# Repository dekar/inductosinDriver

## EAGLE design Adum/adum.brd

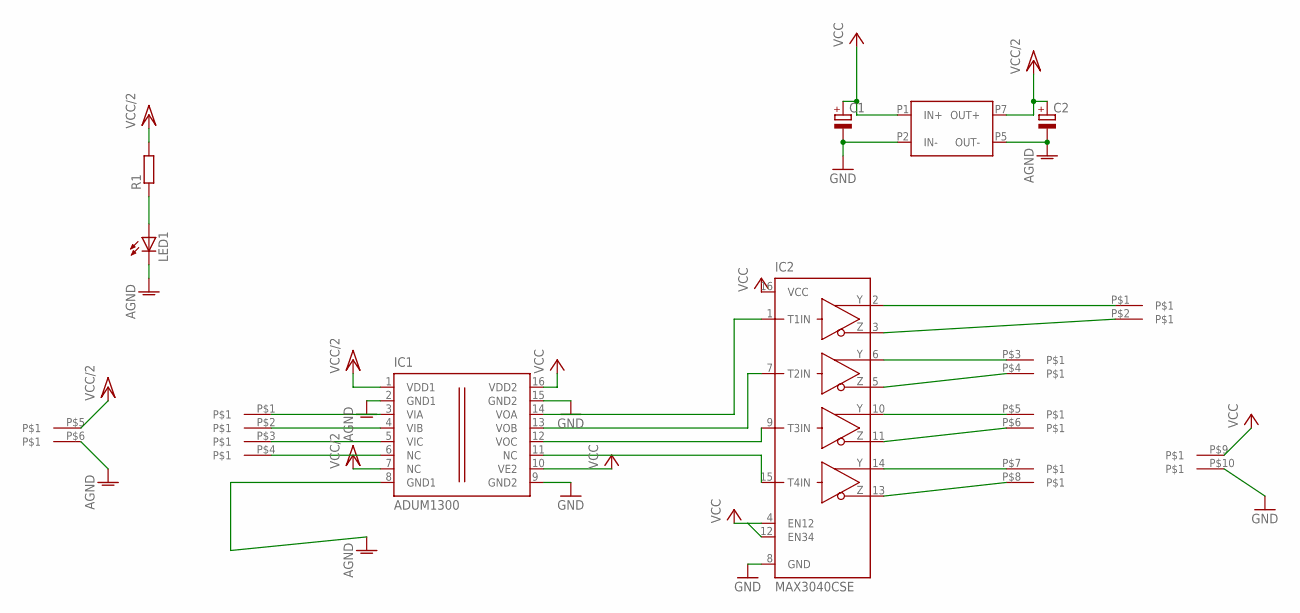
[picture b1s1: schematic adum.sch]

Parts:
C1, C2: CPOL-EUSMCD; SMC_D
IC1: ADUM1300; SO-16W
IC2: MAX3040CSE; SO16
LED1: LEDCHIP-LED0805; CHIP-LED0805
R1: R-EU_M0805; M0805
U$1: 2X5
U$2: 2X3
U$3: DCDC; PWR

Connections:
AGND: C2.-, IC1.2 (GND1), IC1.8 (GND1), LED1.C, U$2.P$6, U$3.P5 (OUT-)
GND: C1.-, IC1.9 (GND2), IC1.15 (GND2), IC2.8 (GND), U$1.P$10, U$3.P2 (IN-)
unnamed: IC1.14 (VOA), IC2.1 (T1IN)
unnamed: IC1.13 (VOB), IC2.7 (T2IN)
unnamed: IC1.12 (VOC), IC2.9 (T3IN)
unnamed: IC1.11 (NC), IC2.15 (T4IN)
unnamed: IC2.3 (Z1), U$1.P$2
unnamed: IC2.2 (Y1), U$1.P$1
unnamed: IC2.11 (Z3), U$1.P$6
unnamed: IC1.6 (NC), U$2.P$4
unnamed: IC1.5 (VIC), U$2.P$3
unnamed: IC2.10 (Y3), U$1.P$5
unnamed: IC1.4 (VIB), U$2.P$2
unnamed: IC2.14 (Y4), U$1.P$7
unnamed: IC2.6 (Y2), U$1.P$3
unnamed: IC1.3 (VIA), U$2.P$1
unnamed: IC2.5 (Z2), U$1.P$4
unnamed: LED1.A, R1.1
unnamed: IC2.13 (Z4), U$1.P$8
VCC: C1.+, IC1.10 (VE2), IC1.16 (VDD2), IC2.4 (EN12), IC2.12 (EN34), IC2.16 (VCC), U$1.P$9, U$3.P1 (IN+)
VCC/2: C2.+, IC1.1 (VDD1), IC1.7 (NC), R1.2, U$2.P$5, U$3.P7 (OUT+)

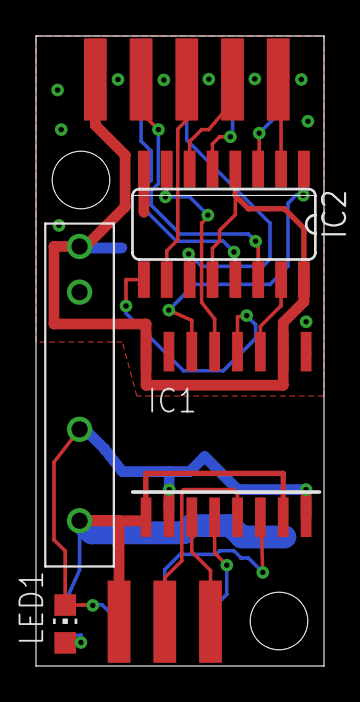
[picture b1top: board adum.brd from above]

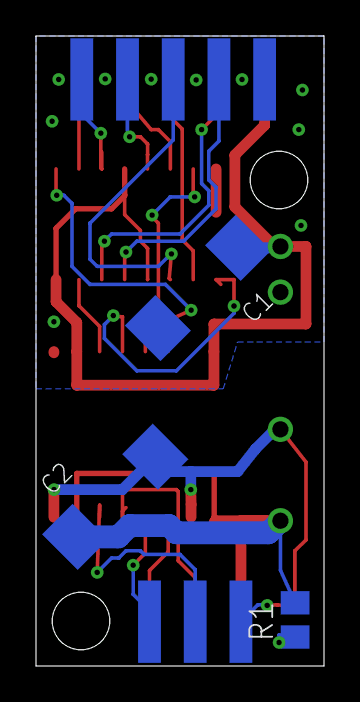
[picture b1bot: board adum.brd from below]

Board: 2 copper layers, 16.0 x 35.0 mm, 9 parts (3 on the bottom side), 21 nets.

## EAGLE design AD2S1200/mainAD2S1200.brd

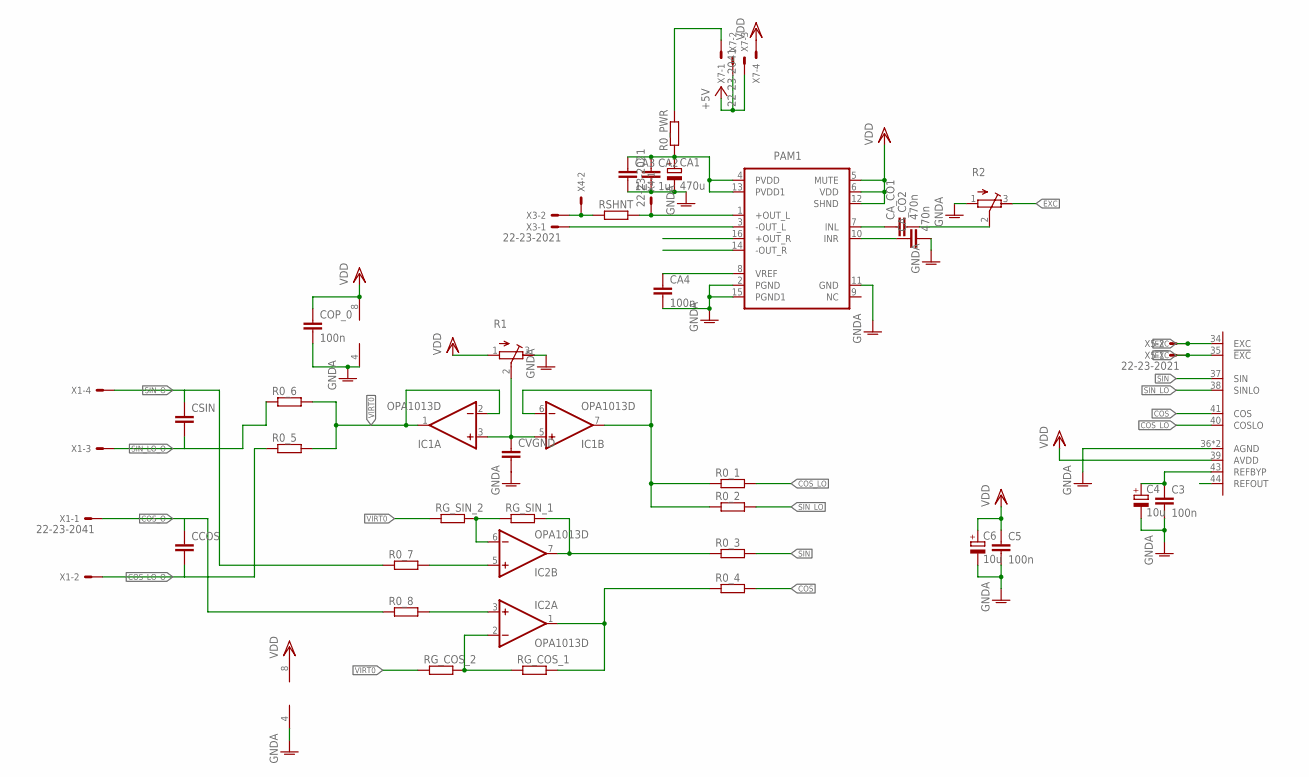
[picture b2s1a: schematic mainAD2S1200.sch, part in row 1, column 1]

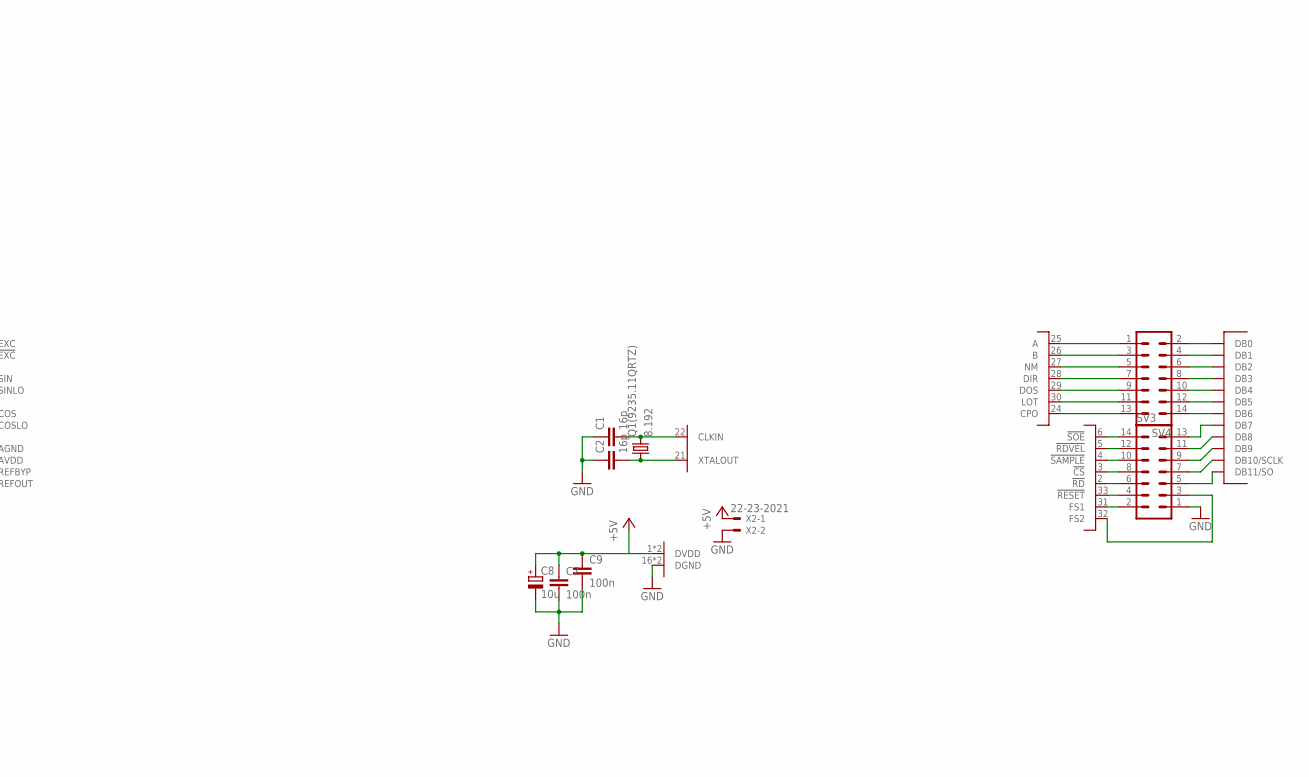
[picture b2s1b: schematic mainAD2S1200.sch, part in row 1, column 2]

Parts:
C1, C2: 16p; C0805
C3, C5, C7, C9: 100n; C0805
C4, C6, C8: 10u; SMC_A
CA1: 470u; EB25D
CA2, CA3: 1u; C1206
CA4: 100n; C0805
CA_CO1, CA_CO2: 470n; C0805
CCOS: C-EUC0805; C0805
COP_0: 100n; C0805
CSIN: C-EUC0805; C0805
CVGND: C-EUC0805; C0805
IC1, IC2: OPA1013D; SO08
PAM1: PAM8403; SOP-16
Q1(9235.11QRTZ): 8.192; CTS406
R0_1, R0_2, R0_3, R0_4, R0_5, R0_6, R0_7, R0_8, R0_PWR: R-EU_R0805; R0805
R1, R2: R-TRIMM64X; RTRIM64X
RG_COS_1, RG_COS_2: R-EU_R0805; R0805
RG_SIN_1, RG_SIN_2: R-EU_R0805; R0805
RSHNT: R-EU_R0805; R0805
SV3, SV4: ML14
U$1: AD1S1200; TQFP-44
X1, X7: 22-23-2041
X2, X3, X4, X5: 22-23-2021

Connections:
!EXC: U$1.35 (!EXC), X5.1
+5V: C7.1, C8.+, C9.1, U$1.1 (DVDD), U$1.17 (DVDD), X2.1, X7.2, X7.3
COS: R0_4.2, U$1.41 (COS)
COS_LO: R0_1.2, U$1.40 (COSLO)
COS_LO_O: CCOS.2, R0_5.1, X1.2
COS_O: CCOS.1, R0_8.1, X1.1
EXC: R2.3 (E), U$1.34 (EXC), X5.2
GND: C1.1, C2.1, C7.2, C8.-, C9.2, SV3.1, U$1.16 (DGND), U$1.23 (DGND), X2.2
GNDA: C3.2, C4.-, C5.2, C6.-, CA1.-, CA2.2, CA3.2, CA4.2, CA_CO2.2, COP_0.2, CVGND.2, IC1.4 (V-), IC2.4 (V-), PAM1.2 (PGND), PAM1.11 (GND), PAM1.15 (PGND1), R1.3 (E), R2.1 (A), U$1.36 (AGND), U$1.42 (AGND)
unnamed: C1.2, Q1(9235.11QRTZ).3 (2), U$1.22 (CLKIN)
unnamed: C2.2, Q1(9235.11QRTZ).1, U$1.21 (XTALOUT)
unnamed: CA4.1, PAM1.8 (VREF)
unnamed: CA_CO1.1, PAM1.7 (INL)
unnamed: C3.1, C4.+, U$1.43 (REFBYP)
unnamed: CA_CO2.1, PAM1.10 (INR)
unnamed: IC1.6 (-IN), IC1.7 (OUT), R0_1.1, R0_2.1
unnamed: PAM1.1 (+OUT_L), RSHNT.2, X4.1
unnamed: PAM1.3 (-OUT_L), X3.1
unnamed: IC2.7 (OUT), R0_3.1, RG_SIN_1.2
unnamed: IC2.1 (OUT), R0_4.1, RG_COS_1.2
unnamed: CVGND.1, IC1.3 (+IN), IC1.5 (+IN), R1.2 (S)
unnamed: SV4.2, U$1.20 (DB0)
unnamed: IC2.5 (+IN), R0_7.2
unnamed: IC2.3 (+IN), R0_8.2
unnamed: SV4.4, U$1.19 (DB1)
unnamed: IC2.6 (-IN), RG_SIN_1.1, RG_SIN_2.2
unnamed: IC2.2 (-IN), RG_COS_1.1, RG_COS_2.2
unnamed: SV4.6, U$1.18 (DB2)
unnamed: SV4.12, U$1.13 (DB5)
unnamed: SV4.14, U$1.12 (DB6)
unnamed: SV4.8, U$1.15 (DB3)
unnamed: SV4.10, U$1.14 (DB4)
unnamed: SV3.5, U$1.7 (DB11/SO)
unnamed: SV3.7, U$1.8 (DB10/SCLK)
unnamed: SV3.9, U$1.9 (DB9)
unnamed: SV3.11, U$1.10 (DB8)
unnamed: SV3.13, U$1.11 (DB7)
unnamed: SV4.11, U$1.30 (LOT)
unnamed: SV4.7, U$1.28 (DIR)
unnamed: SV4.9, U$1.29 (DOS)
unnamed: SV4.5, U$1.27 (NM)
unnamed: SV4.3, U$1.26 (B)
unnamed: SV4.1, U$1.25 (A)
unnamed: SV4.13, U$1.24 (CPO)
unnamed: SV3.6, U$1.2 (!RD)
unnamed: SV3.8, U$1.3 (!CS)
unnamed: SV3.10, U$1.4 (!SAMPLE)
unnamed: SV3.12, U$1.5 (!RDVEL)
unnamed: SV3.14, U$1.6 (!SOE)
unnamed: SV3.4, U$1.33 (!RESET)
unnamed: SV3.2, U$1.31 (FS1)
unnamed: SV3.3, U$1.32 (FS2)
unnamed: CA_CO1.2, R2.2 (S)
unnamed: RSHNT.1, X3.2, X4.2
unnamed: CA1.+, CA2.1, CA3.1, PAM1.4 (PVDD), PAM1.13 (PVDD1), R0_PWR.1
unnamed: R0_PWR.2, X7.1
SIN: R0_3.2, U$1.37 (SIN)
SIN_LO: R0_2.2, U$1.38 (SINLO)
SIN_LO_O: CSIN.2, R0_6.1, X1.3
SIN_O: CSIN.1, R0_7.1, X1.4
VDD: C5.1, C6.+, COP_0.1, IC1.8 (V+), IC2.8 (V+), PAM1.5 (MUTE), PAM1.6 (VDD), PAM1.12 (SHND), R1.1 (A), U$1.39 (AVDD), X7.4
VIRT0: IC1.1 (OUT), IC1.2 (-IN), R0_5.2, R0_6.2, RG_COS_2.1, RG_SIN_2.1

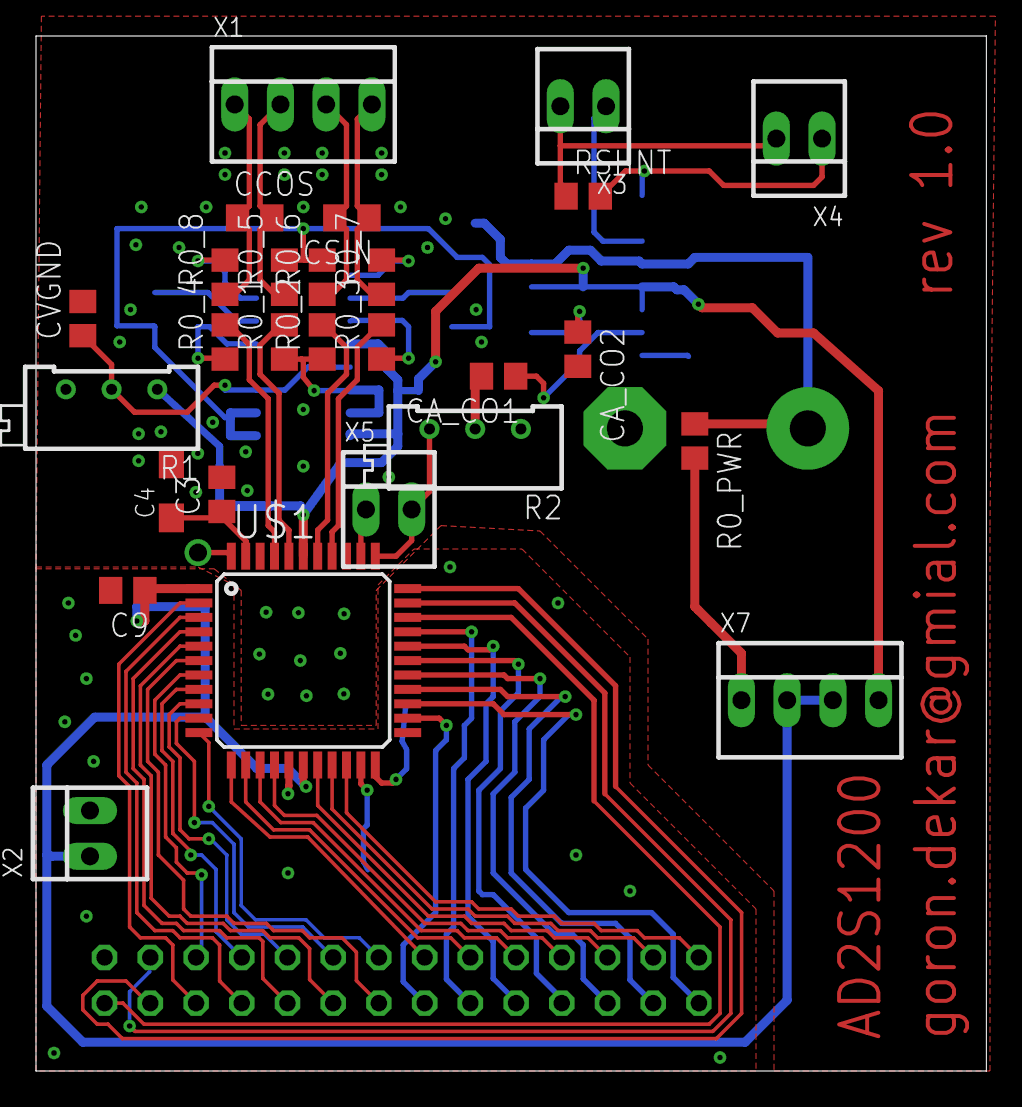
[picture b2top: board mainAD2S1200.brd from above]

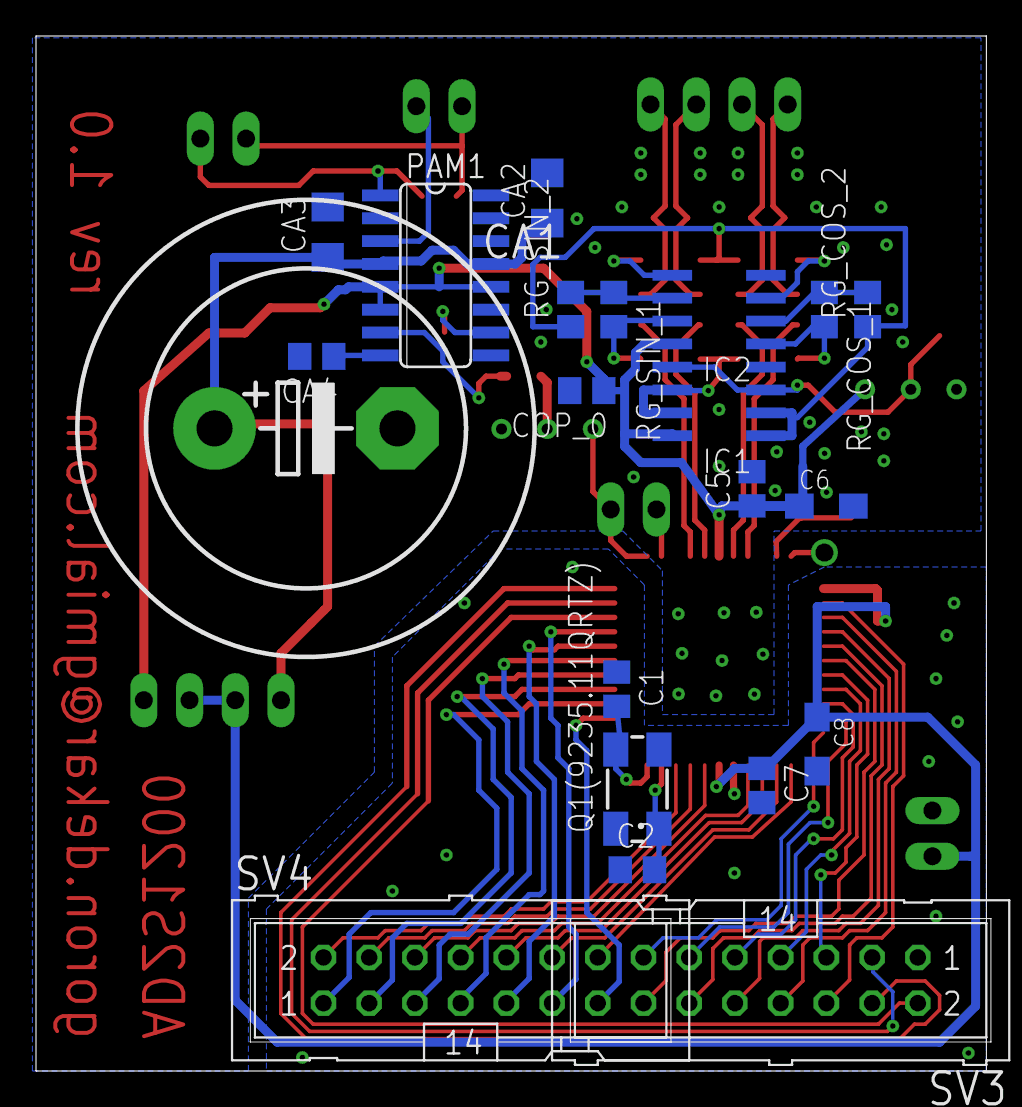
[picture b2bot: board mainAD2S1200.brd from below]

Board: 2 copper layers, 52.8 x 57.5 mm, 48 parts (21 on the bottom side), 62 nets.

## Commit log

2017-11-28 add only AD2S schematic
2017-12-03 Update PDF
2017-12-08 Rev 1.0
